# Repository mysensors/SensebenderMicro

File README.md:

# Sensebender Micro

This is a micro sensor module for Mysensors project: http://www.mysensors.org

Designed to run on 2 x AA(A) batteries, depending on how often one would
like to replace the batteries. 

The sensor includes the following peripherals

- Si7021 Temperature / Humidity sensor (Connected to I2C bus)
- Jedec compatible eeprom/flash footprint
- ATSHA204A for authentication
- LED

The following pins are available on headers:

- Powersupply (1.8 -> 3.5V)
- SDA / SCL (I2C bus)
- A0 / A1
- D3 / D4 / D5 / D6 / D7
- 6 pin ISP port
- 8 pin standard NRF24L01+ connector layout
- FTDI header for serial

*Please note*

MAXIMUM allowed supply voltage is 3.5V, anything above this WILL fry both
Si7021, flash and NRF24 radio module. There is NO voltage regulator on board (To keep
supply current down to a minimum)

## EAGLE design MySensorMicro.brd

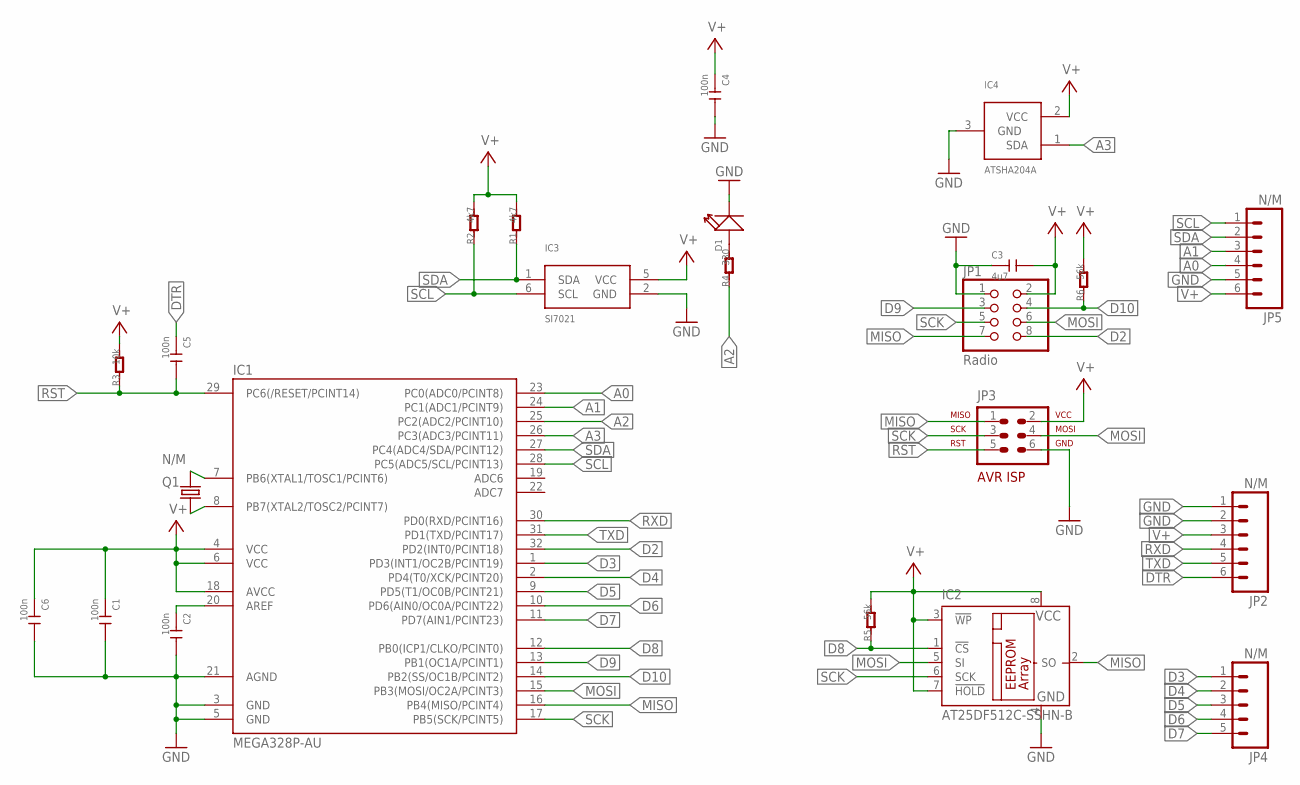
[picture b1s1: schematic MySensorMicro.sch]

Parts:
C1, C2, C4, C5, C6: 100n; C0402
C3: 4u7; C0603
D1: LED-0402
IC1: MEGA328P-AU; TQFP32-08
IC2: AT25DF512C-SSHN-B; SO-08
IC3: SI7021; DFN6
IC4: ATSHA204A; SOT23
JP1: Radio; 2X04
JP2, JP5: N/M; 1X06_NO_SILK
JP3: N/M; AVR-ISP-6
JP4: N/M; 1X05_NO_SILK
Q1: N/M; 2P-L3.2XW1.5MM
R1, R2: 4k7; R0402
R3: 10k; R0402
R4: 330; R0402
R5, R6: 56k; R0402

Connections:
A0: IC1.23 (PC0(ADC0/PCINT8)), JP5.4
A1: IC1.24 (PC1(ADC1/PCINT9)), JP5.3
A2: IC1.25 (PC2(ADC2/PCINT10)), R4.1
A3: IC1.26 (PC3(ADC3/PCINT11)), IC4.1 (SDA)
D2: IC1.32 (PD2(INT0/PCINT18)), JP1.8
D3: IC1.1 (PD3(INT1/OC2B/PCINT19)), JP4.1
D4: IC1.2 (PD4(T0/XCK/PCINT20)), JP4.2
D5: IC1.9 (PD5(T1/OC0B/PCINT21)), JP4.3
D6: IC1.10 (PD6(AIN0/OC0A/PCINT22)), JP4.4
D7: IC1.11 (PD7(AIN1/PCINT23)), JP4.5
D8: IC1.12 (PB0(ICP1/CLKO/PCINT0)), IC2.1 (!CS), R5.1
D9: IC1.13 (PB1(OC1A/PCINT1)), JP1.3
D10: IC1.14 (PB2(SS/OC1B/PCINT2)), JP1.4, R6.1
DTR: C5.1, JP2.6
GND: C1.2, C2.2, C3.1, C4.2, C6.2, D1.-, IC1.3 (GND), IC1.5 (GND), IC1.21 (AGND), IC2.4 (GND), IC3.2 (GND), IC4.3 (GND), JP1.1, JP2.1, JP2.2, JP3.6, JP5.5
MISO: IC1.16 (PB4(MISO/PCINT4)), IC2.2 (SO), JP1.7, JP3.1
MOSI: IC1.15 (PB3(MOSI/OC2A/PCINT3)), IC2.5 (SI), JP1.6, JP3.4
unnamed: IC1.7 (PB6(XTAL1/TOSC1/PCINT6)), Q1.1
unnamed: IC1.8 (PB7(XTAL2/TOSC2/PCINT7)), Q1.2
unnamed: D1.+, R4.2
unnamed: C2.1, IC1.20 (AREF)
RST: C5.2, IC1.29 (PC6(/RESET/PCINT14)), JP3.5, R3.1
RXD: IC1.30 (PD0(RXD/PCINT16)), JP2.4
SCK: IC1.17 (PB5(SCK/PCINT5)), IC2.6 (SCK), JP1.5, JP3.3
SCL: IC1.28 (PC5(ADC5/SCL/PCINT13)), IC3.6 (SCL), JP5.1, R2.1
SDA: IC1.27 (PC4(ADC4/SDA/PCINT12)), IC3.1 (SDA), JP5.2, R1.1
TXD: IC1.31 (PD1(TXD/PCINT17)), JP2.5
V+: C1.1, C3.2, C4.1, C6.1, IC1.4 (VCC), IC1.6 (VCC), IC1.18 (AVCC), IC2.3 (!WP), IC2.7 (!HOLD), IC2.8 (VCC), IC3.5 (VCC), IC4.2 (VCC), JP1.2, JP2.3, JP3.2, JP5.6, R1.2, R2.2, R3.2, R5.2, R6.2

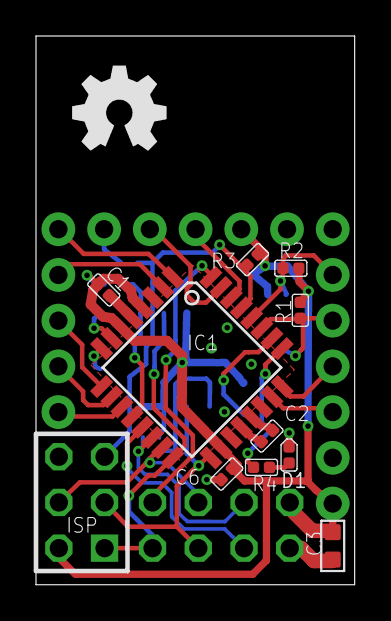
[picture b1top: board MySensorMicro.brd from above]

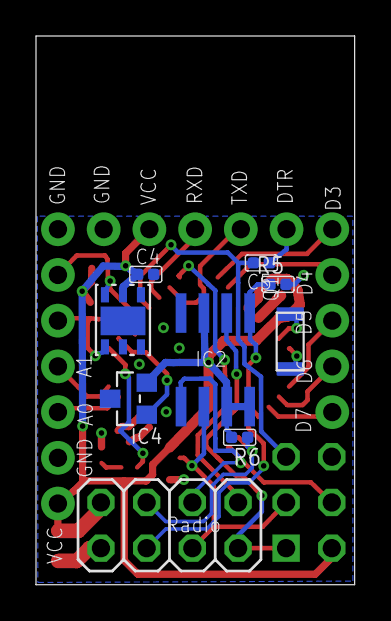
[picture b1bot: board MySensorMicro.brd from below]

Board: 2 copper layers, 17.7 x 30.5 mm, 23 parts (9 on the bottom side), 28 nets.

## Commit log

2015-01-25 Updated readme file
2015-01-25 Cleaned up routing here and there, moved crystal slightly..
2015-01-28 Updated with graphics, sendt to dirtypcbs.com for manufacturing
2015-03-01 Updated part number for external flash
2015-04-01 Updated board layout
2015-04-09 Updated with pullup on both CSN on NRF module, and CE on external flash
2015-04-28 Updated component values on R5/R6
2015-05-03 Updated name
2015-06-08 Added pdf of schematic
2016-03-13 Updated component values on R5/R6
    Fix error > Board and schematic are not consistent! No
    forward-/backannotation will be performed!
    Changes are done using Eagle 7.3.0
2016-03-20 Added BOM file
2016-03-20 Corrected readme file
2016-03-20 Added license files
2016-07-09 Added SensebenderMicro example sketch
2016-07-27 typo
2017-01-23 Fix controller config api change
2017-05-13 Make sure data are sent as expected
    1)Before the fix it took 1 more cycle than expected before the data were sent. Corrected now.
    2)Small fix in threshold checking
2017-06-13 Removed low frequency operation
    the switch to lower frequency operation is not needed, as the battery life is not reduced dramatically, and it confuses users more than necessary, when communication is borked after aprox. 5 minutes 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
2021-09-11 Present BATT_SENSOR as sensorType S_MULTIMETER
    As msgBatt has variable-type 'V_VOLTAGE' it needs type 'S_MULTIMETER'.
    Without this the entity is not being displayed in Home Assistant.

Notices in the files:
parts and their libraries:
SparkFun-Connectors: Licensing: Creative Commons ShareAlike 4.0 International - https://creativecommons.org/licenses/by-sa/4.0
